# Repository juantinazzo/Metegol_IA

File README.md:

# Metegol_IA
Proyecto Final 2018 - (Código atado con alambre)

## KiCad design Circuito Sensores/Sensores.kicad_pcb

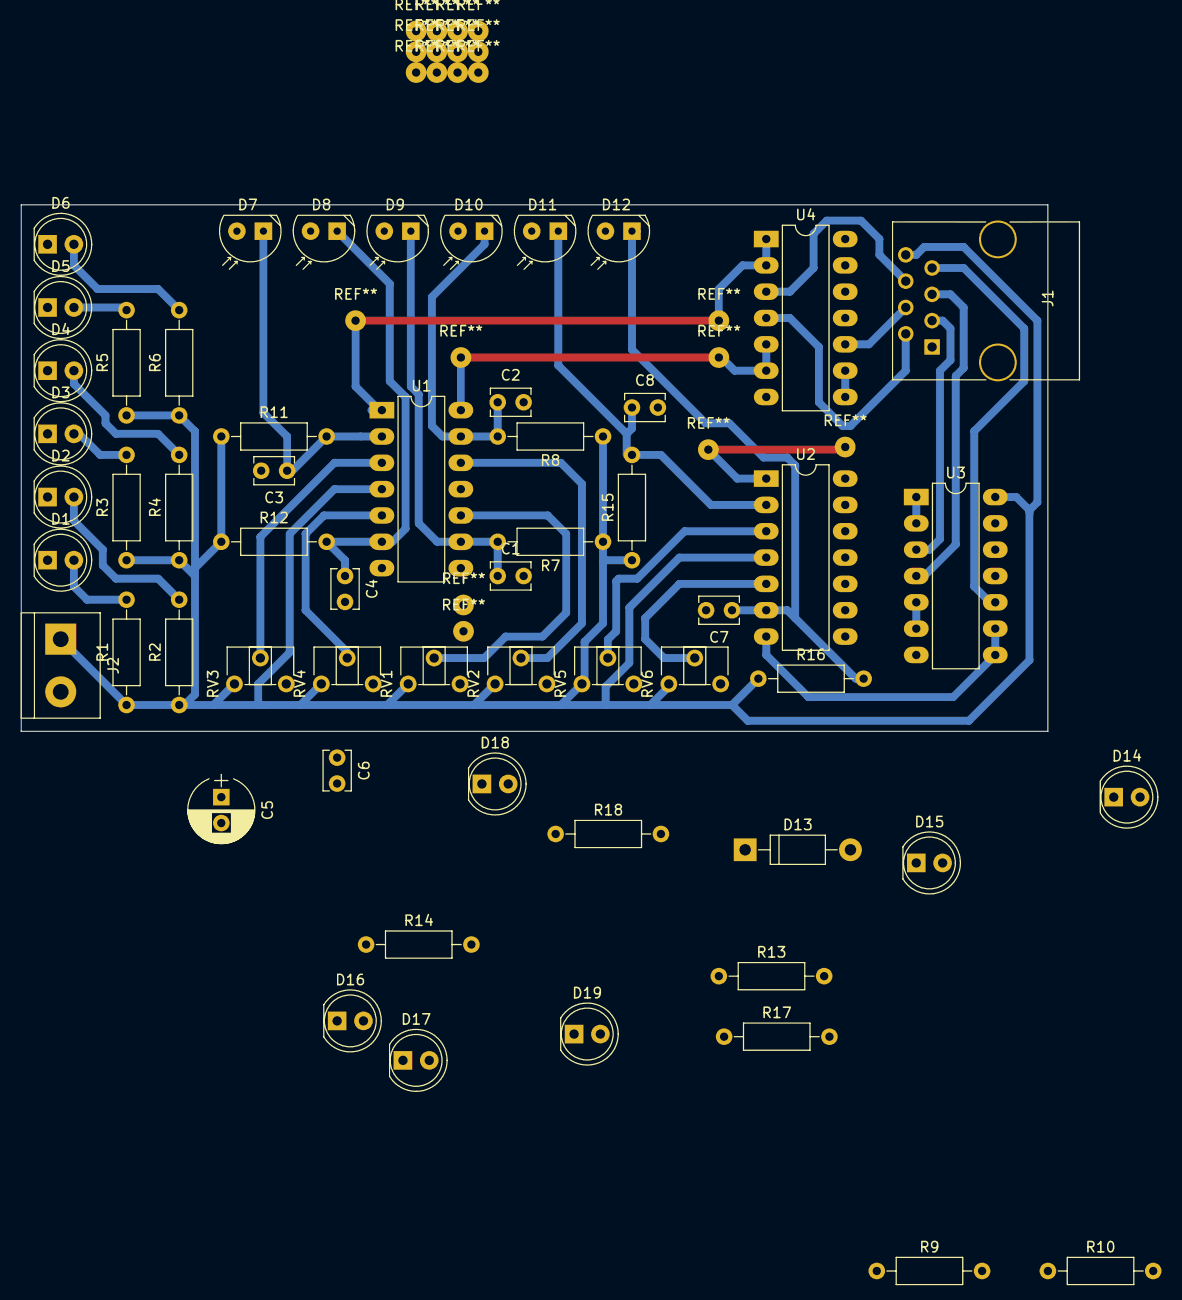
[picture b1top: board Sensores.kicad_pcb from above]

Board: 2 copper layers, 99.1 x 50.8 mm, 57 parts (0 on the bottom side), 38 nets.

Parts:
C1, C2, C3, C4, C6, C7, C8: 100nF; C_Disc_D3.8mm_W2.6mm_P2.50mm
C5: 100uF; CP_Radial_D6.3mm_P2.50mm
D1, D2, D3, D4, D5, D6, D14, D15, D16, D17, D18, D19: LED; LED_D5.0mm
D7, D8, D9, D10, D11, D12: D_Photo; PhotoDiode_SFH205
D13: 1N4007; D_DO-41_SOD81_P10.16mm_Horizontal
J1: RJ45; RJ45_8
J2: CONN_01X02; TerminalBlock_bornier-2_P5.08mm
R1, R2, R3, R4, R5, R6: 470R; R_Axial_DIN0207_L6.3mm_D2.5mm_P10.16mm_Horizontal
R7, R8, R9, R10, R11, R12, R13, R14, R15, R16, R17, R18: R; R_Axial_DIN0207_L6.3mm_D2.5mm_P10.16mm_Horizontal
RV1, RV2, RV3, RV4, RV5, RV6: POT_TRIM; Potentiometer_Trimmer_ACP_CA6h_Vertical
U1, U2: LM324; DIP-14_W7.62mm_LongPads
U3, U4: 4093; DIP-14_W7.62mm_LongPads

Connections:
+5V: C5.1, C6.1, D13.1, J1.8, J2.1, R1.1, R2.1, R3.1, R4.1, R5.1, R6.1, R7.1, R8.1, R11.1, R12.1, R15.1, R16.1, RV1.1, RV2.1, RV3.1, RV4.1, RV5.1, RV6.1, U1.4, U3.14, U4.14
GND: C1.2, C2.2, C3.2, C4.2, C5.2, C6.2, C7.2, C8.2, D1.1, D2.1, D3.1, D4.1, D5.1, D6.1, D7.2, D8.2, D9.2, D10.2, D11.2, D12.2, D13.2, D14.1, D15.1, D16.1, D17.1, D18.1, D19.1, J1.1, J2.2, RV1.3, RV2.3, RV3.3, RV4.3, RV5.3, RV6.3, U1.11, U3.7, U4.7
unnamed: C1.1, D9.1, R7.2, U1.9
unnamed: C2.1, D10.1, R8.2, U1.13
unnamed: C3.1, D7.1, R11.2, U1.2
unnamed: C4.1, D8.1, R12.2, U1.6
unnamed: C7.1, D12.1, R16.2, U2.6
unnamed: C8.1, D11.1, R15.2, U2.2
unnamed: D1.2, R1.2
unnamed: D2.2, R2.2
unnamed: D3.2, R3.2
unnamed: D4.2, R4.2
unnamed: D5.2, R5.2
unnamed: D6.2, R6.2
unnamed: D14.2, R9.2
unnamed: D15.2, R10.2
unnamed: D16.2, R13.2
unnamed: D17.2, R14.2
unnamed: D18.2, R17.2
unnamed: D19.2, R18.2
unnamed: RV1.2, U1.10
unnamed: RV2.2, U1.12
unnamed: RV3.2, U1.3
unnamed: RV4.2, U1.5
unnamed: RV5.2, U2.3
unnamed: RV6.2, U2.5
unnamed: U1.1, U4.1, U4.2
unnamed: U1.7, U3.5, U3.6
unnamed: U1.8, U3.1, U3.2
unnamed: U1.14, U4.5, U4.6
unnamed: U2.1, U4.8, U4.9
unnamed: U2.7, U3.8, U3.9
OUT1: J1.2, R10.1, U4.4
OUT2: J1.3, R9.1, U3.3
OUT3: J1.4, R18.1, U4.10
OUT4: J1.5, R14.1, U3.4
OUT5: J1.6, R13.1, U4.3
OUT6: J1.7, R17.1, U3.10
